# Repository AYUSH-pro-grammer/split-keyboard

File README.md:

# Split Keyboard

Split keyboard created in kicad and cad

## What is this project

This is a split keyboard. It is divided into 2 parts.
I designed it to gain some experience in pcb design, cad modeling and firmware development.
It has 22 keys per side, oled display, and rotary encoder.

## Why I made it

I want to design my own keyboard to gain experience in hardware project.
I got a lot of useful information about creating schematics, pcb routing, footprints, cad case modeling and file structure on github.

## what is inside

- split keyboard pcb
- cad case 
- firmware file
- gerber files
- project images
- bom csv

## Images

### Schematic Left

### Schematic Right

### PCB Routing

### PCB 3D Front

### PCB 3D Back

### 3D 1

### 3D 2

### PCB Order

### Keycaps

### Cherry MX Switches

### Repository Organization

```text
split-keyboard/
│
├── README.md
├── split-keyboard-bom.csv
│
├── cad/
│   ├── assembled.f3z
│   ├── assembled.step
│   └── pcb3d[pcb only].step
│
├── grb/
│   ├── split-keyboard-kicad-B_Cu.gbr
│   ├── split-keyboard-kicad-B_Mask.gbr
│   ├── split-keyboard-kicad-B_Paste.gbr
│   ├── split-keyboard-kicad-B_Silkscreen.gbr
│   ├── split-keyboard-kicad-Edge_Cuts.gbr
│   ├── split-keyboard-kicad-F_Cu.gbr
│   ├── split-keyboard-kicad-F_Mask.gbr
│   ├── split-keyboard-kicad-F_Paste.gbr
│   ├── split-keyboard-kicad-F_Silkscreen.gbr
│   ├── split-keyboard-kicad-NPTH.drl
│   ├── split-keyboard-kicad-PTH.drl
│   └── split-keyboard-kicad-job.gbr

```

## Features

* split keyboard design
* 22 keys on each side
* oled display
* 2 rotary encoders
* custom pcb designed in kicad
* custom cad case
* raspberry pi pico controller
* firmware written in c++

## 3D Model

### Full Keyboard Assembly

IMAGE COMMING SOONN AFTER BUILD...

this is the complete 3d model of the split keyboard with all major components placed inside the design. the model was created to verify the fit of the pcb, switches, display, rotary encoders, and case before manufacturing.

## Firmware

the firmware files for this project are available in the `split_keyboard_firmware/` folder.

currently the firmware is still being developed and tested. basic project structure, display examples, and source files have already been added to the repository.

## build notes

- i used kicad for my schematics and PCB design
- i designed the keyboard case in cad
- i exported gerber files for manufacture
- i kept the design simple to make it easy to build and code

## BOM

| Name | Purpose | Quantity | Total Cost (USD) | Link | Distributor |
| --- | --- | ---: | ---: | --- | --- |
| raspberry pi pico board | devboard to code on | 2 | $8.11 | https://robu.in/product/raspberry-pi-pico/ | robu |
| rotary encoder | knob control | 2 | $4.00 | https://robu.in/product/hongyan-ec11h-7ce15p1zy15f7-rotary-encoder-with-push-button-switch-vertical-plug-in/ | robu |
| pcb | to soilder all things onn | 1 | $46.00 | https://robu.in/product/online-pcb-manufacturing-service/ | robu |
| keycaps | to put above mx keys which give more surface area to click the button | 1 | $22.00 | https://meckeys.com/shop/accessories/keyboard-accessories/keycaps/astronaut-keycap-set/ | meckeys |
| mx cherry keys | to make button works, it is the buttons to press | 44 | $17.00 | https://www.amazon.in/Keyboard-Switches-Dust-Proof-Keycap-Puller/dp/B0GZVJZP6V/ref=sr_1_1?crid=1EHWTYDETVJK0&dib=eyJ2IjoiMSJ9.EPKf_Chov9UdC52FZTZhqD9gxnQ2H53JUXcx-ExCRIuWW5M0qEhEaj_EA4Hh8svkmQaRo_iwuATTiiKnUm_249SRJG3SZchNICn6NqN_LnjG7vWbbi8DNZnYo_UyOs1PBskO9rMlKtHwcH0_-CwgYq2Hd9GEhnLxf2cab6ss66qjs4INdDIkbpSQtbI0jD_gbd9Xzn6TXAXXerfTdFoA0XUWCOw7caRT4xZMyWuczbQ.EnDgPv4DcOxBSh3BzIr-p_Og38qAgpwU2yX1HpgDfDA&dib_tag=se&keywords=cherry+mx+switches&nsdOptOutParam=true&qid=1782203293&sprefix=mx+cherry%2Caps%2C295&sr=8-1 | amazon |
| 1N4148 diodes | key matrix isolation | 44 | $3.00 | https://robu.in/product/diode-1n4148/ | robu |

## note

this project is still being worked on, and i will keep improving the case, layout, and code.

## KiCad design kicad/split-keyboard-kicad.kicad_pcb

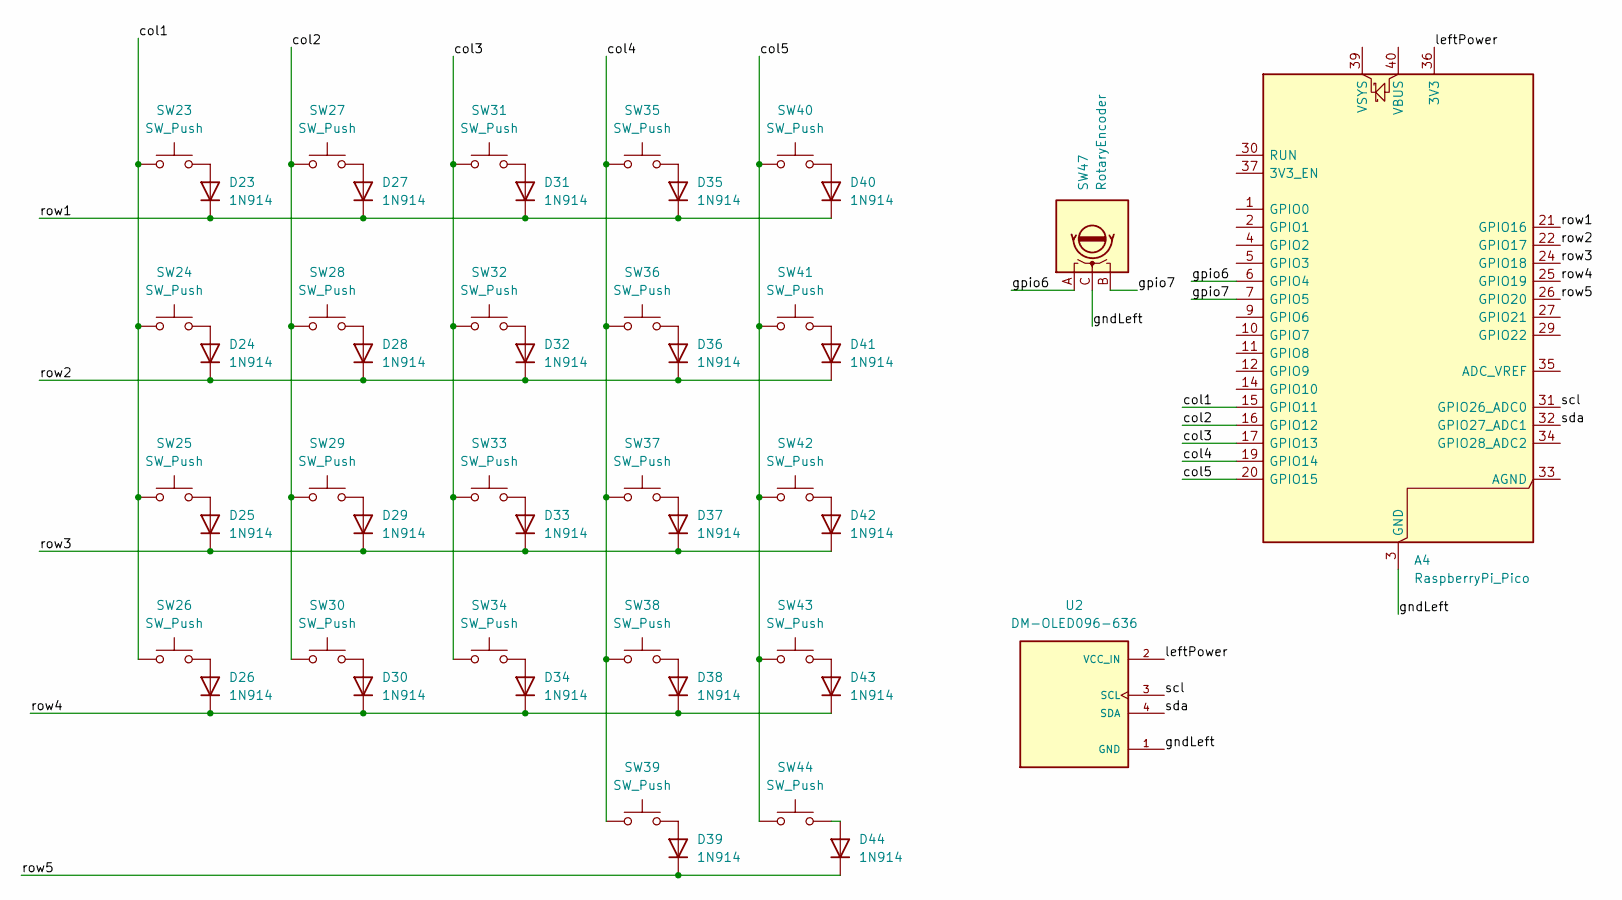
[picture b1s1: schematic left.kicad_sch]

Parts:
A4: RaspberryPi_Pico; RaspberryPi_Pico_Common_Unspecified
D23, D24, D25, D26, D27, D28, D29, D30, D31, D32, D33, D34, D35, D36, D37, D38, D39, D40, D41, D42, D43, D44: 1N914; D_DO-35_SOD27_P7.62mm_Horizontal
SW23, SW24, SW25, SW26, SW27, SW28, SW29, SW30, SW31, SW32, SW33, SW34, SW35, SW36, SW37, SW38, SW39, SW40, SW41, SW42, SW43, SW44: SW_Push; SW_Cherry_MX_1.00u_PCB
SW47: RotaryEncoder; RotaryEncoder_Alps_EC11E-Switch_Vertical_H20mm
U2: DM-OLED096-636; MODULE_DM-OLED096-636; PARTREV 2018-09-10

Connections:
/left/col1: A4.15 (GPIO11), SW23.1, SW24.1, SW25.1, SW26.1
/left/col2: A4.16 (GPIO12), SW27.1, SW28.1, SW29.1, SW30.1
/left/col3: A4.17 (GPIO13), SW31.1, SW32.1, SW33.1, SW34.1
/left/col4: A4.19 (GPIO14), SW35.1, SW36.1, SW37.1, SW38.1, SW39.1
/left/col5: A4.20 (GPIO15), SW40.1, SW41.1, SW42.1, SW43.1, SW44.1
/left/gndLeft: A4.3 (GND), A4.8 (GND), A4.13 (GND), A4.18 (GND), A4.23 (GND), A4.28 (GND), A4.38 (GND), SW47.C, U2.1 (GND)
/left/gpio6: A4.6 (GPIO4), SW47.A
/left/gpio7: A4.7 (GPIO5), SW47.B
/left/leftPower: A4.36 (3V3), U2.2 (VCC_IN)
/left/row1: A4.21 (GPIO16), D23.1 (K), D27.1 (K), D31.1 (K), D35.1 (K), D40.1 (K)
/left/row2: A4.22 (GPIO17), D24.1 (K), D28.1 (K), D32.1 (K), D36.1 (K), D41.1 (K)
/left/row3: A4.24 (GPIO18), D25.1 (K), D29.1 (K), D33.1 (K), D37.1 (K), D42.1 (K)
/left/row4: A4.25 (GPIO19), D26.1 (K), D30.1 (K), D34.1 (K), D38.1 (K), D43.1 (K)
/left/row5: A4.26 (GPIO20), D39.1 (K), D44.1 (K)
/left/scl: A4.31 (GPIO26_ADC0), U2.3 (SCL)
/left/sda: A4.32 (GPIO27_ADC1), U2.4 (SDA)
unnamed: D23.2 (A), SW23.2
unnamed: D24.2 (A), SW24.2
unnamed: D25.2 (A), SW25.2
unnamed: D26.2 (A), SW26.2
unnamed: D27.2 (A), SW27.2
unnamed: D28.2 (A), SW28.2
unnamed: D29.2 (A), SW29.2
unnamed: D30.2 (A), SW30.2
unnamed: D31.2 (A), SW31.2
unnamed: D32.2 (A), SW32.2
unnamed: D33.2 (A), SW33.2
unnamed: D34.2 (A), SW34.2
unnamed: D35.2 (A), SW35.2
unnamed: D36.2 (A), SW36.2
unnamed: D37.2 (A), SW37.2
unnamed: D38.2 (A), SW38.2
unnamed: D39.2 (A), SW39.2
unnamed: D40.2 (A), SW40.2
unnamed: D41.2 (A), SW41.2
unnamed: D42.2 (A), SW42.2
unnamed: D43.2 (A), SW43.2
unnamed: D44.2 (A), SW44.2

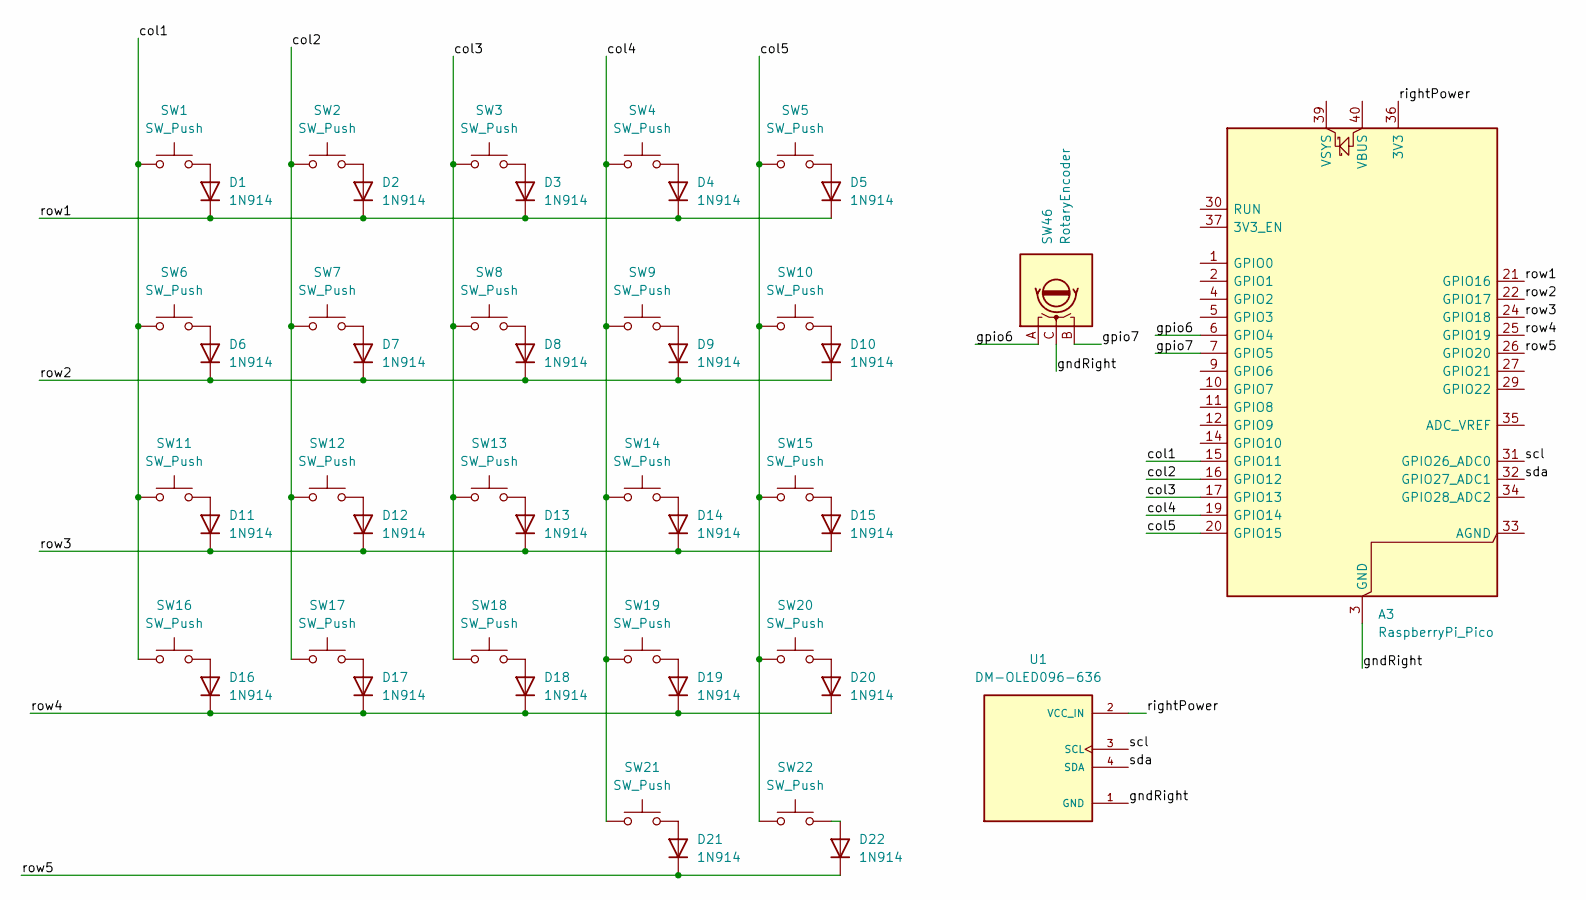
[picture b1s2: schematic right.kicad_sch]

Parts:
A3: RaspberryPi_Pico; RaspberryPi_Pico_Common_Unspecified
D1, D2, D3, D4, D5, D6, D7, D8, D9, D10, D11, D12, D13, D14, D15, D16, D17, D18, D19, D20, D21, D22: 1N914; D_DO-35_SOD27_P7.62mm_Horizontal
SW1, SW2, SW3, SW4, SW5, SW6, SW7, SW8, SW9, SW10, SW11, SW12, SW13, SW14, SW15, SW16, SW17, SW18, SW19, SW20, SW21, SW22: SW_Push; SW_Cherry_MX_1.00u_PCB
SW46: RotaryEncoder; RotaryEncoder_Alps_EC11E-Switch_Vertical_H20mm
U1: DM-OLED096-636; MODULE_DM-OLED096-636; PARTREV 2018-09-10

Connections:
/right/col1: A3.15 (GPIO11), SW1.1, SW6.1, SW11.1, SW16.1
/right/col2: A3.16 (GPIO12), SW2.1, SW7.1, SW12.1, SW17.1
/right/col3: A3.17 (GPIO13), SW3.1, SW8.1, SW13.1, SW18.1
/right/col4: A3.19 (GPIO14), SW4.1, SW9.1, SW14.1, SW19.1, SW21.1
/right/col5: A3.20 (GPIO15), SW5.1, SW10.1, SW15.1, SW20.1, SW22.1
/right/gndRight: A3.3 (GND), A3.8 (GND), A3.13 (GND), A3.18 (GND), A3.23 (GND), A3.28 (GND), A3.38 (GND), SW46.C, U1.1 (GND)
/right/gpio6: A3.6 (GPIO4), SW46.A
/right/gpio7: A3.7 (GPIO5), SW46.B
/right/rightPower: A3.36 (3V3), U1.2 (VCC_IN)
/right/row1: A3.21 (GPIO16), D1.1 (K), D2.1 (K), D3.1 (K), D4.1 (K), D5.1 (K)
/right/row2: A3.22 (GPIO17), D6.1 (K), D7.1 (K), D8.1 (K), D9.1 (K), D10.1 (K)
/right/row3: A3.24 (GPIO18), D11.1 (K), D12.1 (K), D13.1 (K), D14.1 (K), D15.1 (K)
/right/row4: A3.25 (GPIO19), D16.1 (K), D17.1 (K), D18.1 (K), D19.1 (K), D20.1 (K)
/right/row5: A3.26 (GPIO20), D21.1 (K), D22.1 (K)
/right/scl: A3.31 (GPIO26_ADC0), U1.3 (SCL)
/right/sda: A3.32 (GPIO27_ADC1), U1.4 (SDA)
unnamed: D1.2 (A), SW1.2
unnamed: D2.2 (A), SW2.2
unnamed: D3.2 (A), SW3.2
unnamed: D4.2 (A), SW4.2
unnamed: D5.2 (A), SW5.2
unnamed: D6.2 (A), SW6.2
unnamed: D7.2 (A), SW7.2
unnamed: D8.2 (A), SW8.2
unnamed: D9.2 (A), SW9.2
unnamed: D10.2 (A), SW10.2
unnamed: D11.2 (A), SW11.2
unnamed: D12.2 (A), SW12.2
unnamed: D13.2 (A), SW13.2
unnamed: D14.2 (A), SW14.2
unnamed: D15.2 (A), SW15.2
unnamed: D16.2 (A), SW16.2
unnamed: D17.2 (A), SW17.2
unnamed: D18.2 (A), SW18.2
unnamed: D19.2 (A), SW19.2
unnamed: D20.2 (A), SW20.2
unnamed: D21.2 (A), SW21.2
unnamed: D22.2 (A), SW22.2

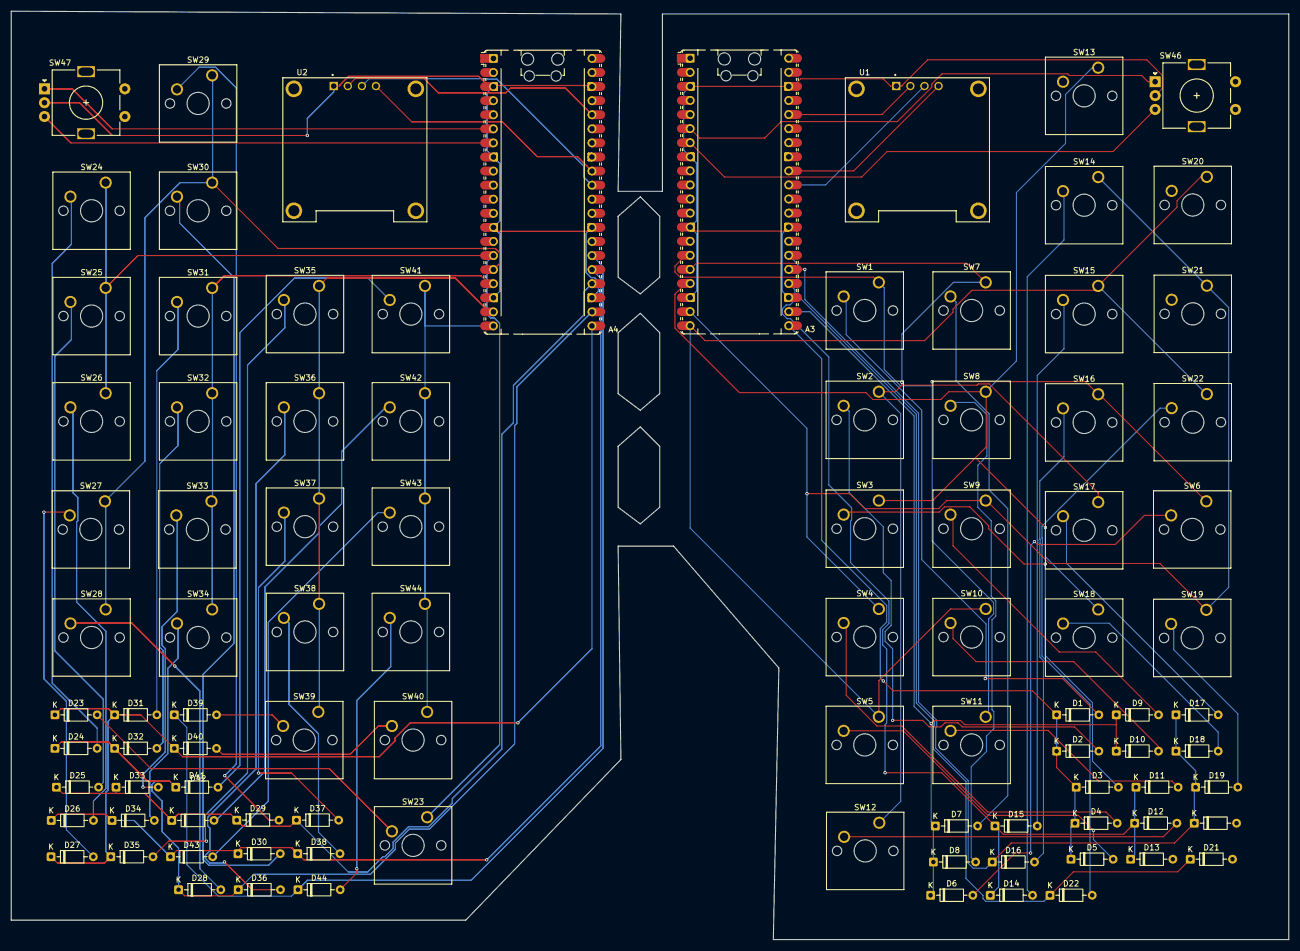
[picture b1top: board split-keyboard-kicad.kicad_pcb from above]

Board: 2 copper layers, 230.5 x 167.5 mm, 94 parts (0 on the bottom side), 76 nets.

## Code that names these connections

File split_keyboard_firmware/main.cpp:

#include <Arduino.h>
#include <Keyboard.h>
#include <Wire.h>
#include <Adafruit_GFX.h>
#include <Adafruit_SSD1306.h>

/*
Split Keyboard Firmware Package

File names:
- main.cpp      : Split keyboard firmware for a single Pico per half
- oled_demo.cpp : OLED demo sketch
- platformio.ini : PlatformIO Arduino project file

Pin configuration according to your schematic:
- Row pins: GPIO16, 17, 18, 19, 20
- Col pins: GPIO11, 12, 13, 14, 15
- Rotary encoder pins: GPIO6, GPIO7
- OLED I2C: GPIO26 = SCL, GPIO27 = SDA
- OLED address: 0x3C

*/

#define SIDE_LEFT 1

static constexpr uint8_t ROWS = 5;
static constexpr uint8_t COLS = 5;
static constexpr uint8_t DEBOUNCE_MS = 18;

static constexpr uint8_t ROW_PINS[ROWS] = {16, 17, 18, 19, 20};
static constexpr uint8_t COL_PINS[COLS] = {11, 12, 13, 14, 15};

static constexpr uint8_t ENC_A = 6;
static constexpr uint8_t ENC_B = 7;

static constexpr uint8_t OLED_SDA = 27;
static constexpr uint8_t OLED_SCL = 26;
static constexpr uint8_t OLED_ADDR = 0x3C;

static constexpr int SCREEN_W = 128;
static constexpr int SCREEN_H = 64;

Adafruit_SSD1306 display(SCREEN_W, SCREEN_H, &Wire, -1);

struct DebouncedKey {
  bool raw = false;
  bool stable = false;
  uint32_t changed_at = 0;
};

static DebouncedKey keys[ROWS][COLS];
static bool oled_ok = false;
static uint32_t last_oled = 0;
static uint32_t last_scan = 0;

static int32_t encoder_steps = 0;
static int32_t encoder_detents = 0;
static uint8_t enc_prev = 0;

static char last_key_label[16] = "none";
static uint16_t active_keys = 0;
static uint16_t total_presses = 0;

// Common split layout; edit only these arrays to match your preferred keymap.
static const uint8_t keymap_left[ROWS][COLS] = {
  { 'q', 'w', 'e', 'r', 't' },
  { 'a', 's', 'd', 'f', 'g' },
  { 'z', 'x', 'c', 'v', 'b' },
  { KEY_LEFT_CTRL, KEY_LEFT_GUI, KEY_LEFT_ALT, ' ', KEY_BACKSPACE },
  { 0, 0, 0, KEY_ESC, KEY_TAB },
};

static const uint8_t keymap_right[ROWS][COLS] = {
  { 'y', 'u', 'i', 'o', 'p' },
  { 'h', 'j', 'k', 'l', ';' },
  { 'n', 'm', ',', '.', '/' },
  { KEY_LEFT_SHIFT, KEY_RETURN, KEY_DELETE, KEY_UP_ARROW, KEY_DOWN_ARROW },
  { 0, 0, 0, KEY_PAGE_UP, KEY_PAGE_DOWN },
};

static inline const uint8_t (*active_keymap())[COLS] {
  return SIDE_LEFT ? keymap_left : keymap_right;
}

static const char* side_name() {
  return SIDE_LEFT ? "LEFT" : "RIGHT";
}

static void setLastKeyLabel(uint8_t code, bool down) {
  if (code == 0) {
    snprintf(last_key_label, sizeof(last_key_label), "unused");
    return;
  }

  if (code >= 32 && code <= 126) {
    snprintf(last_key_label, sizeof(last_key_label), "%c %s", (char)code, down ? "dn" : "up");
    return;
  }

  switch (code) {
    case KEY_RETURN:       snprintf(last_key_label, sizeof(last_key_label), "ENTER %s", down ? "dn" : "up"); break;
    case KEY_ESC:          snprintf(last_key_label, sizeof(last_key_label), "ESC %s", down ? "dn" : "up"); break;
    case KEY_TAB:          snprintf(last_key_label, sizeof(last_key_label), "TAB %s", down ? "dn" : "up"); break;
    case KEY_BACKSPACE:    snprintf(last_key_label, sizeof(last_key_label), "BSPC %s", down ? "dn" : "up"); break;
    case KEY_DELETE:       snprintf(last_key_label, sizeof(last_key_label), "DEL %s", down ? "dn" : "up"); break;
    case KEY_PAGE_UP:      snprintf(last_key_label, sizeof(last_key_label), "PGUP %s", down ? "dn" : "up"); break;
    case KEY_PAGE_DOWN:    snprintf(last_key_label, sizeof(last_key_label), "PGDN %s", down ? "dn" : "up"); break;
    case KEY_LEFT_CTRL:    snprintf(last_key_label, sizeof(last_key_label), "LCTRL %s", down ? "dn" : "up"); break;
    case KEY_LEFT_SHIFT:   snprintf(last_key_label, sizeof(last_key_label), "LSHFT %s", down ? "dn" : "up"); break;
    case KEY_LEFT_ALT:     snprintf(last_key_label, sizeof(last_key_label), "LALT %s", down ? "dn" : "up"); break;
    case KEY_LEFT_GUI:     snprintf(last_key_label, sizeof(last_key_label), "LGUI %s", down ? "dn" : "up"); break;
    case KEY_UP_ARROW:     snprintf(last_key_label, sizeof(last_key_label), "UP %s", down ? "dn" : "up"); break;
    case KEY_DOWN_ARROW:   snprintf(last_key_label, sizeof(last_key_label), "DOWN %s", down ? "dn" : "up"); break;
    case KEY_LEFT_ARROW:   snprintf(last_key_label, sizeof(last_key_label), "LEFT %s", down ? "dn" : "up"); break;
    case KEY_RIGHT_ARROW:  snprintf(last_key_label, sizeof(last_key_label), "RIGHT %s", down ? "dn" : "up"); break;
    default:               snprintf(last_key_label, sizeof(last_key_label), "KC%u %s", code, down ? "dn" : "up"); break;
  }
}

static void pressKey(uint8_t code) {
  if (code == 0) return;
  Keyboard.press(code);
  total_presses++;
  setLastKeyLabel(code, true);
}

static void releaseKey(uint8_t code) {
  if (code == 0) return;
  Keyboard.release(code);
  setLastKeyLabel(code, false);
}

static void handleKeyChange(uint8_t row, uint8_t col, bool pressed) {
  const uint8_t code = active_keymap()[row][col];
  if (pressed) pressKey(code);
  else releaseKey(code);
}

static uint16_t countActiveKeys() {
  uint16_t count = 0;
  for (uint8_t r = 0; r < ROWS; ++r) {
    for (uint8_t c = 0; c < COLS; ++c) {
      if (keys[r][c].stable) ++count;
    }
  }
  return count;
}

static void initMatrix() {
  for (uint8_t r = 0; r < ROWS; ++r) {
    pinMode(ROW_PINS[r], OUTPUT);
    digitalWrite(ROW_PINS[r], HIGH);
  }
  for (uint8_t c = 0; c < COLS; ++c) {
    pinMode(COL_PINS[c], INPUT_PULLUP);
  }
}

static void initEncoder() {
  pinMode(ENC_A, INPUT_PULLUP);
  pinMode(ENC_B, INPUT_PULLUP);
  enc_prev = (digitalRead(ENC_A) << 1) | digitalRead(ENC_B);
}

static void initOLED() {
  Wire.setSDA(OLED_SDA);
  Wire.setSCL(OLED_SCL);
  Wire.begin();

  oled_ok = display.begin(SSD1306_SWITCHCAPVCC, OLED_ADDR);
  if (!oled_ok) return;

  display.clearDisplay();
  display.setTextSize(1);
  display.setTextColor(SSD1306_WHITE);
  display.setCursor(0, 0);
  display.print("Split keyboard");
  display.setCursor(0, 12);
  display.print(side_name());
  display.display();
}

static void drawOLED() {
  if (!oled_ok) return;

  display.clearDisplay();
  display.setTextSize(1);
  display.setTextColor(SSD1306_WHITE);

  display.setCursor(0, 0);
  display.print("Split keyboard");
  display.setCursor(0, 10);
  display.print("Side: ");
  display.print(side_name());

  display.setCursor(0, 20);
  display.print("Active: ");
  display.print(active_keys);

  display.setCursor(0, 30);
  display.print("Enc: ");
  display.print(encoder_detents);

  display.setCursor(0, 40);
  display.print("Keys: ");
  display.print(total_presses);

  display.setCursor(0, 52);
  display.print(last_key_label);

  // tiny animation
  uint8_t x = (millis() / 18) % 104;
  display.drawRect(x, 56, 24, 6, SSD1306_WHITE);
  display.fillRect(x + 2, 58, 10, 2, SSD1306_WHITE);

  display.display();
}

static void scanEncoder() {
  // Simple quadrature decode with detent accumulation.
  static const int8_t lut[16] = {
    0, -1,  1,  0,
    1,  0,  0, -1,
   -1,  0,  0,  1,
    0,  1, -1,  0
  };

  const uint8_t curr = (digitalRead(ENC_A) << 1) | digitalRead(ENC_B);
  const uint8_t idx = (enc_prev << 2) | curr;
  const int8_t delta = lut[idx];
  enc_prev = curr;

  if (delta == 0) return;

  encoder_steps += delta;

  // four transitions per detent on most EC11-style encoders
  if (encoder_steps >= 4) {
    encoder_steps = 0;
    encoder_detents++;
    Keyboard.write(KEY_PAGE_UP);
    snprintf(last_key_label, sizeof(last_key_label), "ENC cw");
  } else if (encoder_steps <= -4) {
    encoder_steps = 0;
    encoder_detents--;
    Keyboard.write(KEY_PAGE_DOWN);
    snprintf(last_key_label, sizeof(last_key_label), "ENC ccw");
  }
}

static void scanMatrix() {
  const uint32_t now = millis();

  for (uint8_t r = 0; r < ROWS; ++r) {
    digitalWrite(ROW_PINS[r], LOW);
    delayMicroseconds(5);

    for (uint8_t c = 0; c < COLS; ++c) {
      const bool raw_pressed = (digitalRead(COL_PINS[c]) == LOW);

      DebouncedKey &k = keys[r][c];
      if (raw_pressed != k.raw) {
        k.raw = raw_pressed;
        k.changed_at = now;
      }

      if ((now - k.changed_at) >= DEBOUNCE_MS && k.stable != k.raw) {
        k.stable = k.raw;
        handleKeyChange(r, c, k.stable);
      }
    }

    digitalWrite(ROW_PINS[r], HIGH);
  }

  active_keys = countActiveKeys();
}

void setup() {
  delay(300);
  Keyboard.begin();

  initMatrix();
  initEncoder();
  initOLED();

  last_scan = millis();
}

void loop() {
  scanMatrix();
  scanEncoder();

  if (millis() - last_oled >= 80) {
    last_oled = millis();
    drawOLED();
  }

  // If you want to reduce CPU use a little:
  delay(1);
}

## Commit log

2026-06-23 added all
2026-06-23 updated csv
2026-06-23 code added
2026-06-24 updated 3d
